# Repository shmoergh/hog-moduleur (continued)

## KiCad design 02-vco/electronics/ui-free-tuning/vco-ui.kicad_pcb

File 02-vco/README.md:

# Hog Moduleur / VCO

Eurorack compatible VCO.

## Features

- Raw saw generator with classic waveshaper circuits. Triangle, saw and square outputs
- Sub oscillator and noise circuit (can be selected with a jumper)
- Pulse width voltage control for square wave
- High precision over about 10 octaves
- Hard sync input
- FM input
- Two temperature compensation options for flexible DIY build (one is THT only)
- Separate core and UI PCBs for reusability and custom UI builds
- Gerber files for JLCPCB order
- Designed from very common electronic components

## Photos

**IN PROGRESS**

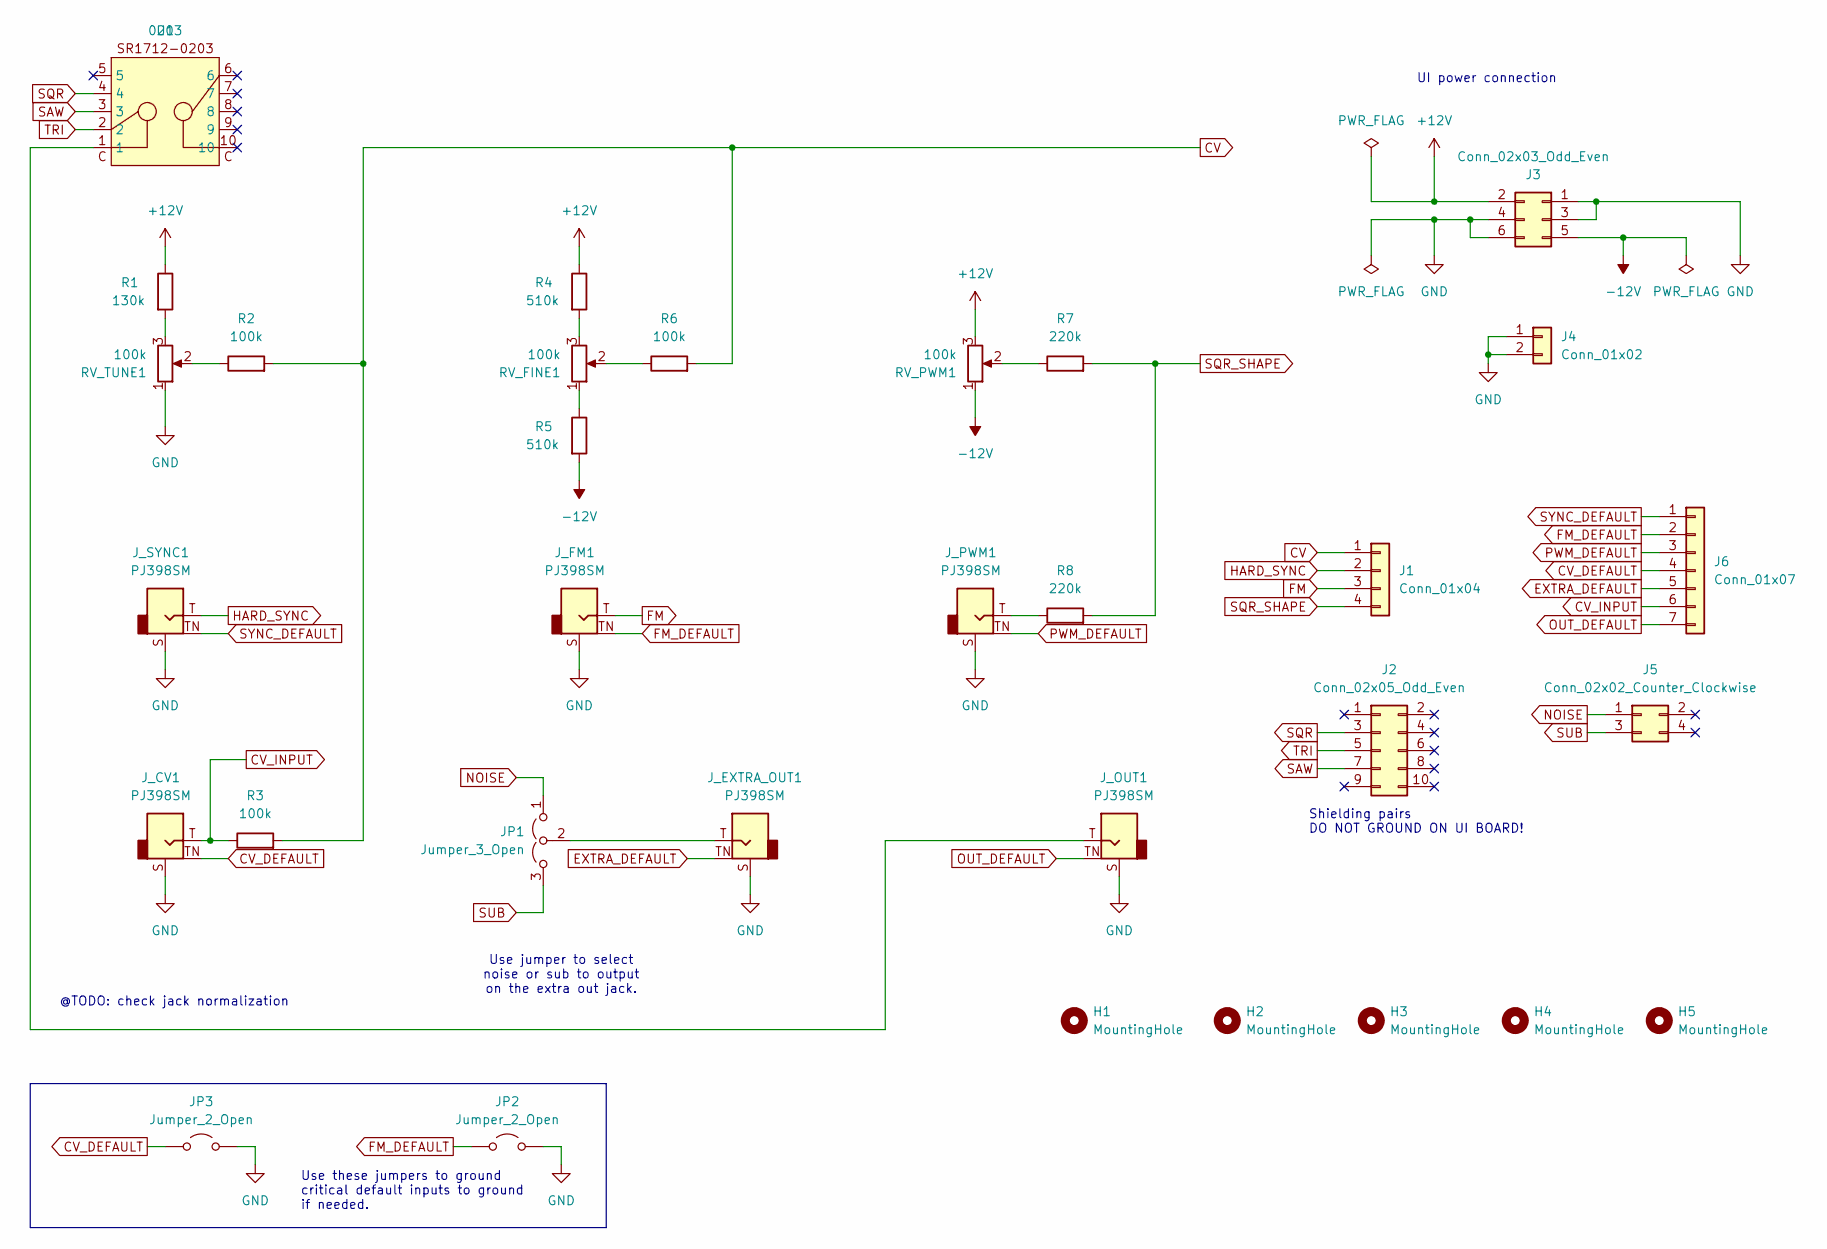
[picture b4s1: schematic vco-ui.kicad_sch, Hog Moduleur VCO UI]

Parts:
H1, H2, H3, H4, H5: MountingHole; MountingHole_3.2mm_M3_DIN965_Pad
J1: Conn_01x04; PinSocket_1x04_P2.54mm_Vertical; Part no. 200-SSW10401TMS
J2: Conn_02x05_Odd_Even; PinSocket_2x05_P2.54mm_Vertical; Part no. 200-SSW10501TD
J3: Conn_02x03_Odd_Even; PinSocket_2x03_P2.54mm_Vertical; Part no. 200-SSW10301TD
J4: Conn_01x02; PinSocket_1x02_P2.54mm_Vertical; Part no. 200-SSW10201TS
J5: Conn_02x02_Counter_Clockwise; PinSocket_2x02_P2.54mm_Vertical; Part no. 200-SSW10206TD
J6: Conn_01x07; PinSocket_1x07_P2.54mm_Vertical; Part no. 200-SSW10601TS
JP1: Jumper_3_Open; PinHeader_1x03_P2.54mm_Horizontal; Part no. 200-HTSW10308TSRA
JP2, JP3: Jumper_2_Open; PinHeader_1x02_P2.54mm_Horizontal; Part no. 200-HTSW10208TSRA
J_CV1: PJ398SM; Jack_3.5mm_QingPu_WQP-PJ398SM_Vertical_CircularHoles; Part no. PJ398SM
J_EXTRA_OUT1: PJ398SM; Jack_3.5mm_QingPu_WQP-PJ398SM_Vertical_CircularHoles; Part no. PJ398SM
J_FM1: PJ398SM; Jack_3.5mm_QingPu_WQP-PJ398SM_Vertical_CircularHoles; Part no. PJ398SM
J_OUT1: PJ398SM; Jack_3.5mm_QingPu_WQP-PJ398SM_Vertical_CircularHoles; Part no. PJ398SM
J_PWM1: PJ398SM; Jack_3.5mm_QingPu_WQP-PJ398SM_Vertical_CircularHoles; Part no. PJ398SM
J_SYNC1: PJ398SM; Jack_3.5mm_QingPu_WQP-PJ398SM_Vertical_CircularHoles; Part no. PJ398SM
R1: 130k; R_Axial_DIN0207_L6.3mm_D2.5mm_P7.62mm_Horizontal
R2, R3, R6: 100k; R_Axial_DIN0207_L6.3mm_D2.5mm_P7.62mm_Horizontal; Part no. 603-MFR-25FRF52100K
R4, R5: 510k; R_Axial_DIN0207_L6.3mm_D2.5mm_P7.62mm_Horizontal
R7, R8: 220k; R_Axial_DIN0207_L6.3mm_D2.5mm_P7.62mm_Horizontal; Part no. 603-MFR-25FRF52-220K
RV_FINE1: 100k; Potentiometer_Bourns_Single-PTV09A; Part no. 652-PTV09A4025FB104
RV_PWM1: 100k; Potentiometer_Bourns_Single-PTV09A; Part no. 652-PTV09A4025FB104
RV_TUNE1: 100k; Potentiometer_Bourns_Single-PTV09A; Part no. 652-PTV09A4025FB104
U1: 0203; SR1712-0203; Part no. 105-SR1712F-23NS

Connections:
+12V: J3.2, R1.1, R4.1, RV_PWM1.3
-12V: J3.5, R5.2, RV_PWM1.1
CV: J1.1, R2.2, R3.2, R6.2
CV_DEFAULT: J6.4, JP3.1 (A), J_CV1.TN
CV_INPUT: J6.6, J_CV1.T, R3.1
EXTRA_DEFAULT: J6.5, J_EXTRA_OUT1.TN
FM: J1.3, J_FM1.T
FM_DEFAULT: J6.2, JP2.1 (A), J_FM1.TN
GND: J3.1, J3.3, J3.4, J3.6, J4.1, J4.2, JP2.2 (B), JP3.2 (B), J_CV1.S, J_EXTRA_OUT1.S, J_FM1.S, J_OUT1.S, J_PWM1.S, J_SYNC1.S, RV_TUNE1.1
HARD_SYNC: J1.2, J_SYNC1.T
NOISE: J5.1, JP1.1 (A)
unnamed: JP1.2 (C), J_EXTRA_OUT1.T
unnamed: J_OUT1.T, U1.1
unnamed: J_PWM1.T, R8.1
unnamed: R1.2, RV_TUNE1.3
unnamed: R2.1, RV_TUNE1.2
unnamed: R4.2, RV_FINE1.3
unnamed: R5.1, RV_FINE1.1
unnamed: R6.1, RV_FINE1.2
unnamed: R7.1, RV_PWM1.2
OUT_DEFAULT: J6.7, J_OUT1.TN
PWM_DEFAULT: J6.3, J_PWM1.TN
SAW: J2.7, U1.3
SQR: J2.3, U1.4
SQR_SHAPE: J1.4, R7.2, R8.2
SUB: J5.3, JP1.3 (B)
SYNC_DEFAULT: J6.1, J_SYNC1.TN
TRI: J2.5, U1.2

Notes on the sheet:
@TODO: check jack normalization
Use these jumpers to ground critical default inputs to ground if needed.
UI power connection
Use jumper to select noise or sub to output on the extra out jack.
Shielding pairs DO NOT GROUND ON UI BOARD!

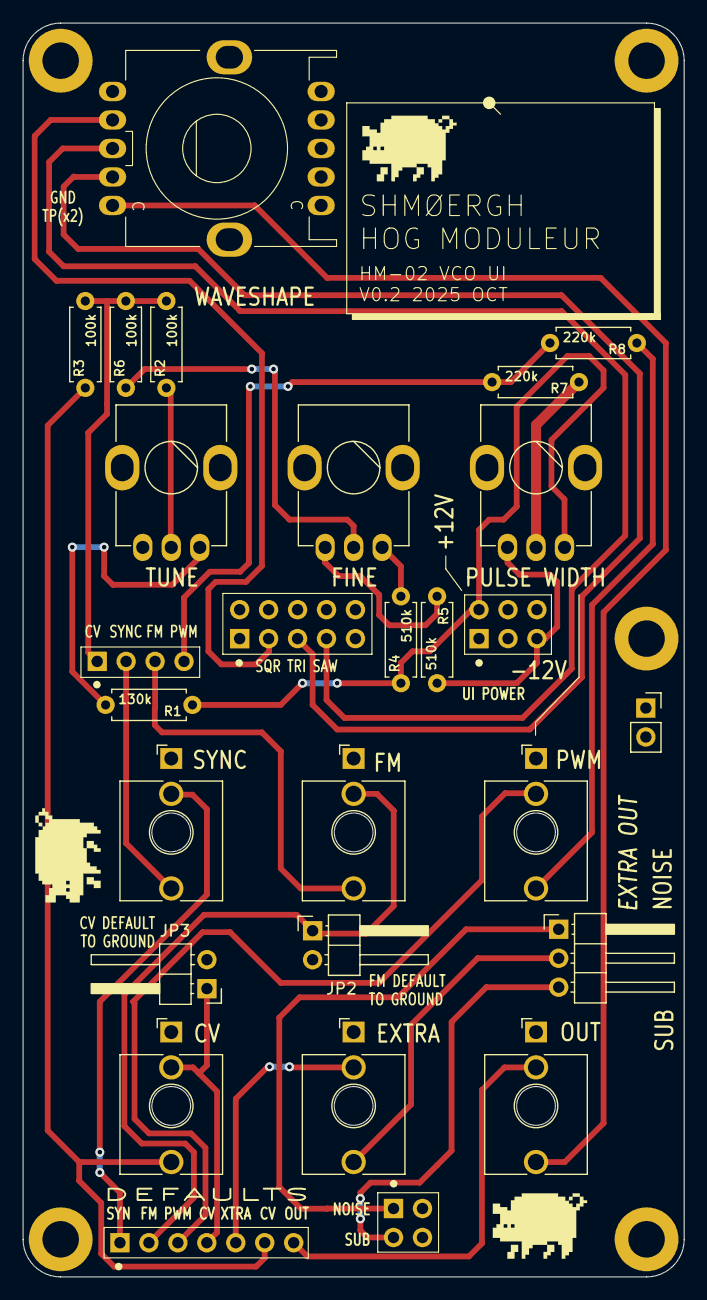
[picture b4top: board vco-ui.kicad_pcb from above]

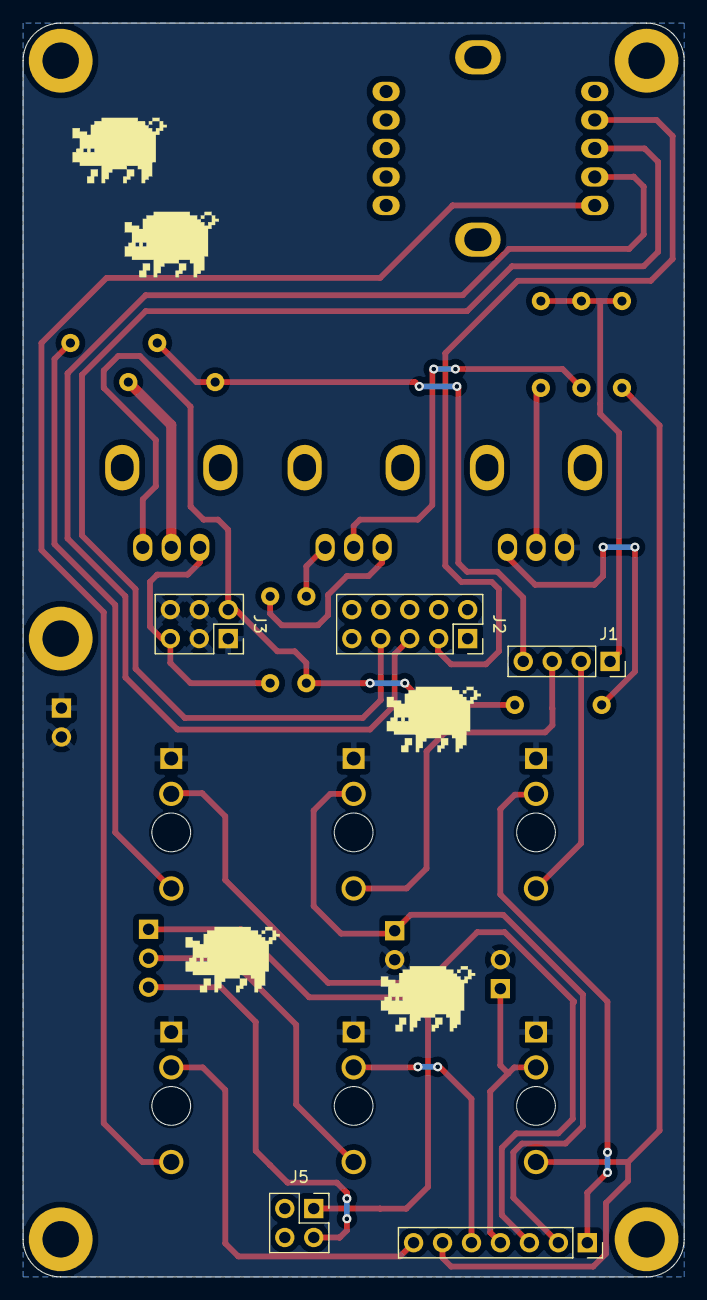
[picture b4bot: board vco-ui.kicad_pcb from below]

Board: 2 copper layers, 58.0 x 110.0 mm, 32 parts (5 on the bottom side), 28 nets.

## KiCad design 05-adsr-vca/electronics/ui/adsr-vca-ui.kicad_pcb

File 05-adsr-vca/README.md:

# Hog Moduleur / ADSR + VCA

TBD

## Status

**IN PROGRESS**

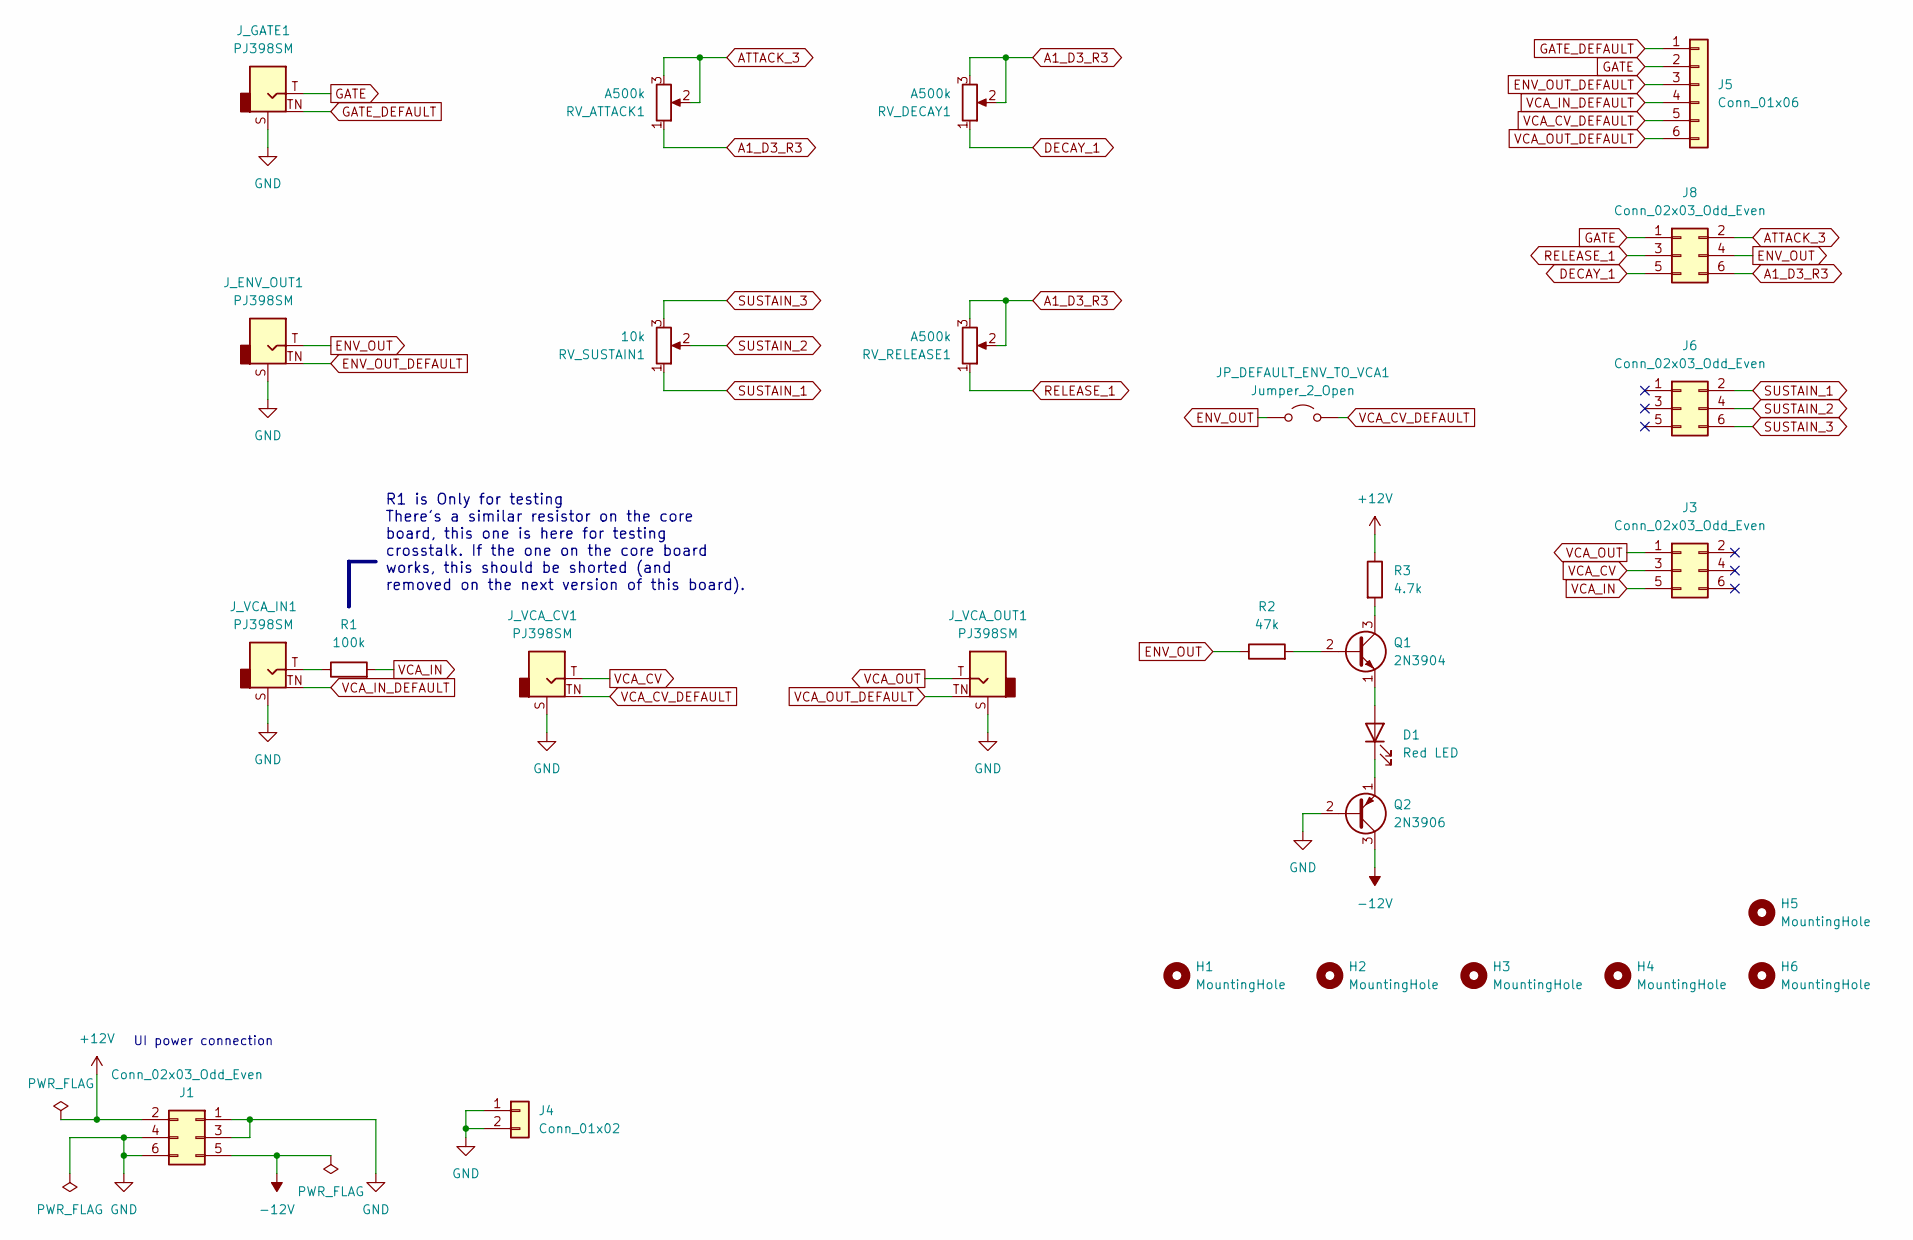
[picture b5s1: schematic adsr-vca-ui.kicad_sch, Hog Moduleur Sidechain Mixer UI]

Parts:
D1: Red LED; LED_D3.0mm
H1, H2, H3, H4, H5, H6: MountingHole; MountingHole_3.2mm_M3_DIN965_Pad
J1: Conn_02x03_Odd_Even; PinSocket_2x03_P2.54mm_Vertical; Part no. 200-SSW10301TD
J3, J6, J8: Conn_02x03_Odd_Even; PinSocket_2x03_P2.54mm_Vertical
J4: Conn_01x02; PinSocket_1x02_P2.54mm_Vertical; Part no. 200-SSW10201TS
J5: Conn_01x06; PinSocket_1x06_P2.54mm_Vertical; Part no. 200-SSW10601TS
JP_DEFAULT_ENV_TO_VCA1: Jumper_2_Open; PinHeader_1x02_P2.54mm_Horizontal
J_ENV_OUT1: PJ398SM; Jack_3.5mm_QingPu_WQP-PJ398SM_Vertical_CircularHoles; Part no. PJ398SM
J_GATE1: PJ398SM; Jack_3.5mm_QingPu_WQP-PJ398SM_Vertical_CircularHoles; Part no. PJ398SM
J_VCA_CV1: PJ398SM; Jack_3.5mm_QingPu_WQP-PJ398SM_Vertical_CircularHoles; Part no. PJ398SM
J_VCA_IN1: PJ398SM; Jack_3.5mm_QingPu_WQP-PJ398SM_Vertical_CircularHoles; Part no. PJ398SM
J_VCA_OUT1: PJ398SM; Jack_3.5mm_QingPu_WQP-PJ398SM_Vertical_CircularHoles; Part no. PJ398SM
Q1: 2N3904; TO-92_Inline_Wide
Q2: 2N3906; TO-92_Inline_Wide
R1: 100k; R_Axial_DIN0207_L6.3mm_D2.5mm_P7.62mm_Horizontal
R2: 47k; R_Axial_DIN0207_L6.3mm_D2.5mm_P7.62mm_Horizontal
R3: 4.7k; R_Axial_DIN0207_L6.3mm_D2.5mm_P7.62mm_Horizontal
RV_ATTACK1: A500k; Potentiometer_Bourns_Single-PTV09A; Part no. 652-PTV09A4025FB104
RV_DECAY1: A500k; Potentiometer_Bourns_Single-PTV09A; Part no. 652-PTV09A4025FB104
RV_RELEASE1: A500k; Potentiometer_Bourns_Single-PTV09A; Part no. 652-PTV09A4025FB104
RV_SUSTAIN1: 10k; TRIM_PTA4543-2015DPB103; Part no. 652-PTV09A4025FB104

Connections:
+12V: J1.2, R3.1
-12V: J1.5, Q2.3 (C)
A1_D3_R3: J8.6, RV_ATTACK1.1, RV_DECAY1.2, RV_DECAY1.3, RV_RELEASE1.2, RV_RELEASE1.3
ATTACK_3: J8.2, RV_ATTACK1.2, RV_ATTACK1.3
DECAY_1: J8.5, RV_DECAY1.1
ENV_OUT: J8.4, JP_DEFAULT_ENV_TO_VCA1.1 (A), J_ENV_OUT1.T, R2.1
ENV_OUT_DEFAULT: J5.3, J_ENV_OUT1.TN
GATE: J5.2, J8.1, J_GATE1.T
GATE_DEFAULT: J5.1, J_GATE1.TN
GND: J1.1, J1.3, J1.4, J1.6, J4.1, J4.2, J_ENV_OUT1.S, J_GATE1.S, J_VCA_CV1.S, J_VCA_IN1.S, J_VCA_OUT1.S, Q2.2 (B)
unnamed: D1.2 (A), Q1.1 (E)
unnamed: D1.1 (K), Q2.1 (E)
unnamed: J_VCA_IN1.T, R1.1
unnamed: Q1.2 (B), R2.2
unnamed: Q1.3 (C), R3.2
RELEASE_1: J8.3, RV_RELEASE1.1
SUSTAIN_1: J6.2, RV_SUSTAIN1.1
SUSTAIN_2: J6.4, RV_SUSTAIN1.2
SUSTAIN_3: J6.6, RV_SUSTAIN1.3
VCA_CV: J3.3, J_VCA_CV1.T
VCA_CV_DEFAULT: J5.5, JP_DEFAULT_ENV_TO_VCA1.2 (B), J_VCA_CV1.TN
VCA_IN: J3.5, R1.2
VCA_IN_DEFAULT: J5.4, J_VCA_IN1.TN
VCA_OUT: J3.1, J_VCA_OUT1.T
VCA_OUT_DEFAULT: J5.6, J_VCA_OUT1.TN

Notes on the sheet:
R1 is Only for testing There's a similar resistor on the core board, this one is here for testing crosstalk. If the one on the core board works, this should be shorted (and removed on the next version of this board).
UI power connection

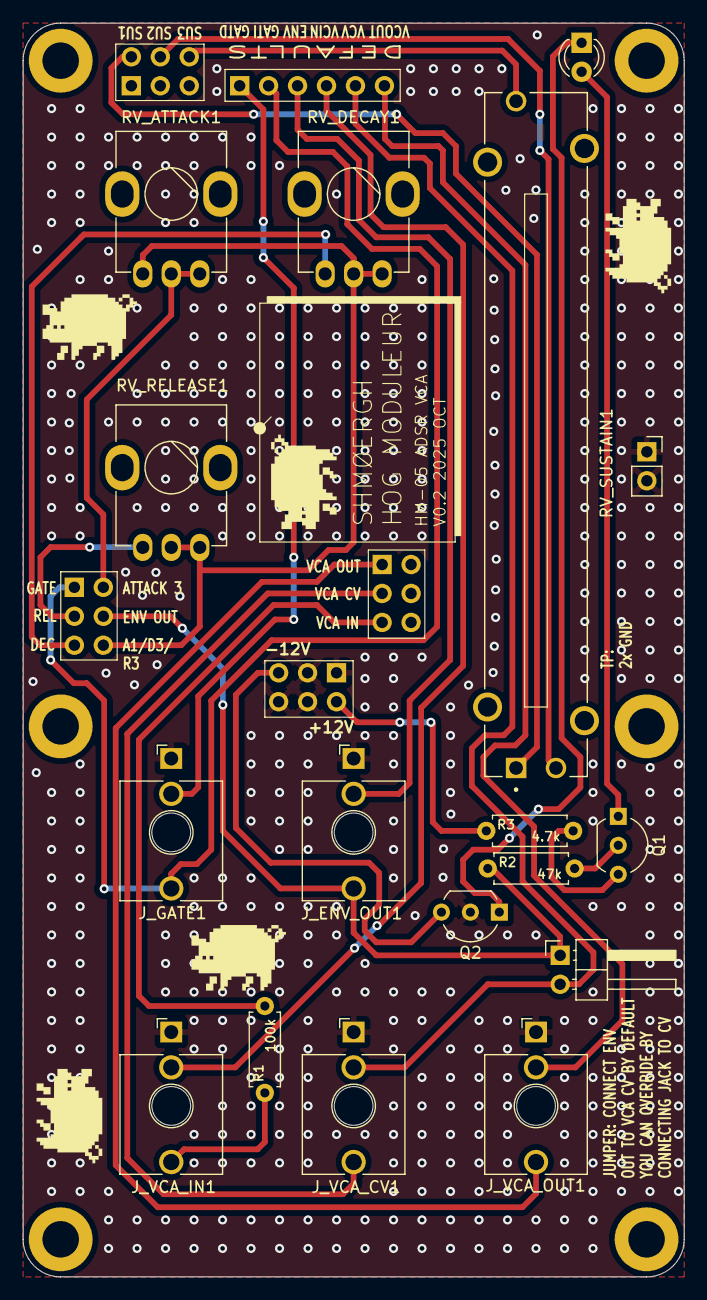
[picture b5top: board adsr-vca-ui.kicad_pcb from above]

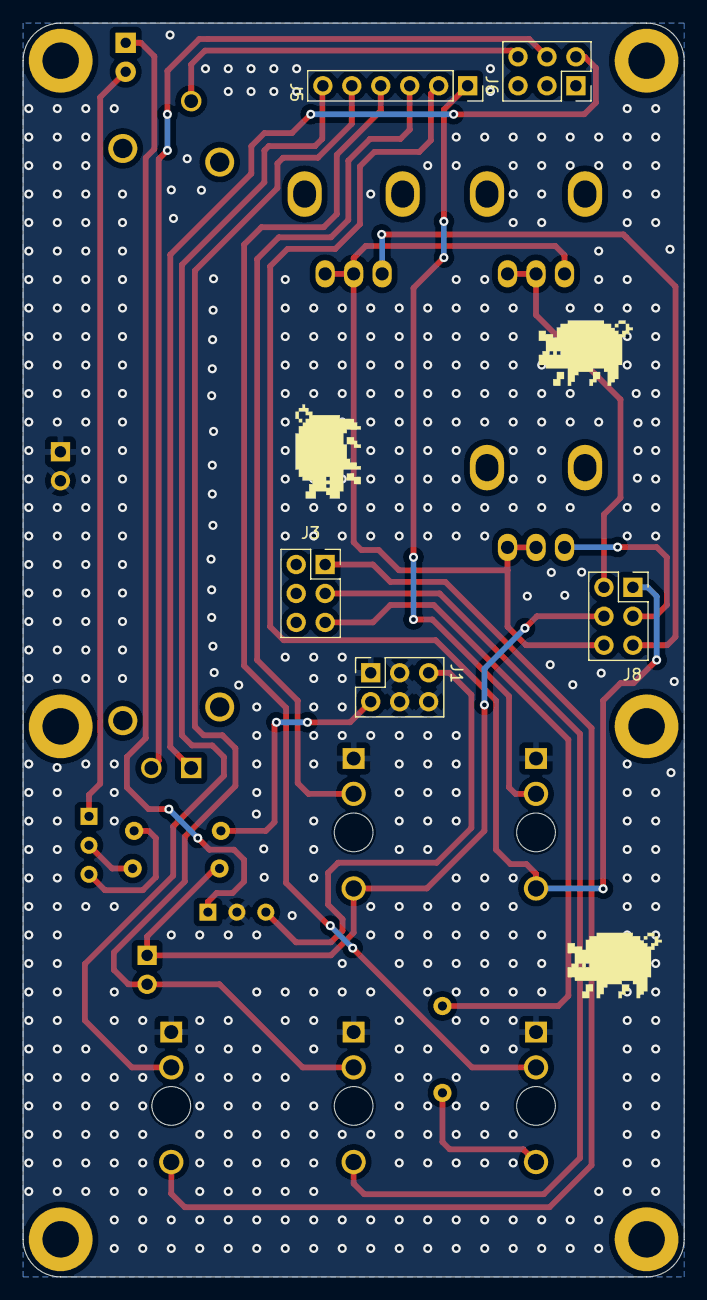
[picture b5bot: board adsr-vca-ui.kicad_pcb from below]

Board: 2 copper layers, 58.0 x 110.0 mm, 28 parts (5 on the bottom side), 25 nets.

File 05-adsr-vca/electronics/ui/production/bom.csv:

Designator,Footprint,Quantity,Value,LCSC Part #
D1,LED_D3.0mm,1,D,
"J1, J3, J6, J8",PinSocket_2x03_P2.54mm_Vertical,4,Conn_02x03_Odd_Even,
J4,PinSocket_1x02_P2.54mm_Vertical,1,Conn_01x02,
J5,PinSocket_1x06_P2.54mm_Vertical,1,Conn_01x06,
JP_DEFAULT_ENV_TO_VCA1,PinHeader_1x02_P2.54mm_Horizontal,1,Jumper_2_Open,
"J_ENV_OUT1, J_GATE1, J_VCA_CV1, J_VCA_IN1, J_VCA_OUT1",Jack_3.5mm_QingPu_WQP-PJ398SM_Vertical_CircularHoles,5,PJ398SM,
"RV_ATTACK1, RV_DECAY1, RV_RELEASE1",Potentiometer_Bourns_Single-PTV09A,3,A500k,
RV_SUSTAIN1,TRIM_PTA4543-2015DPB103,1,10k,

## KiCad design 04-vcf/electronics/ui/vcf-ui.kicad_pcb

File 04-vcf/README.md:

# Hog Moduleur / VCF

Dual mode Eurorack compatible diode filter based on the famous Synthacon Steiner-Parker circuit.

## Features

- Classic diode filter with extremely drippy character
- Low pass and high pass filter inputs
- Fine-tunable maximum resonance control — can go smooth to crazy
- Two external CV inputs with logarithmic attenuverters
- Optional EMC shielding to isolate external noise
- Separate core and UI PCBs for reusability and custom UI builds
- Gerber files for JLCPCB order
- Designed from very common electronic components

## Photos

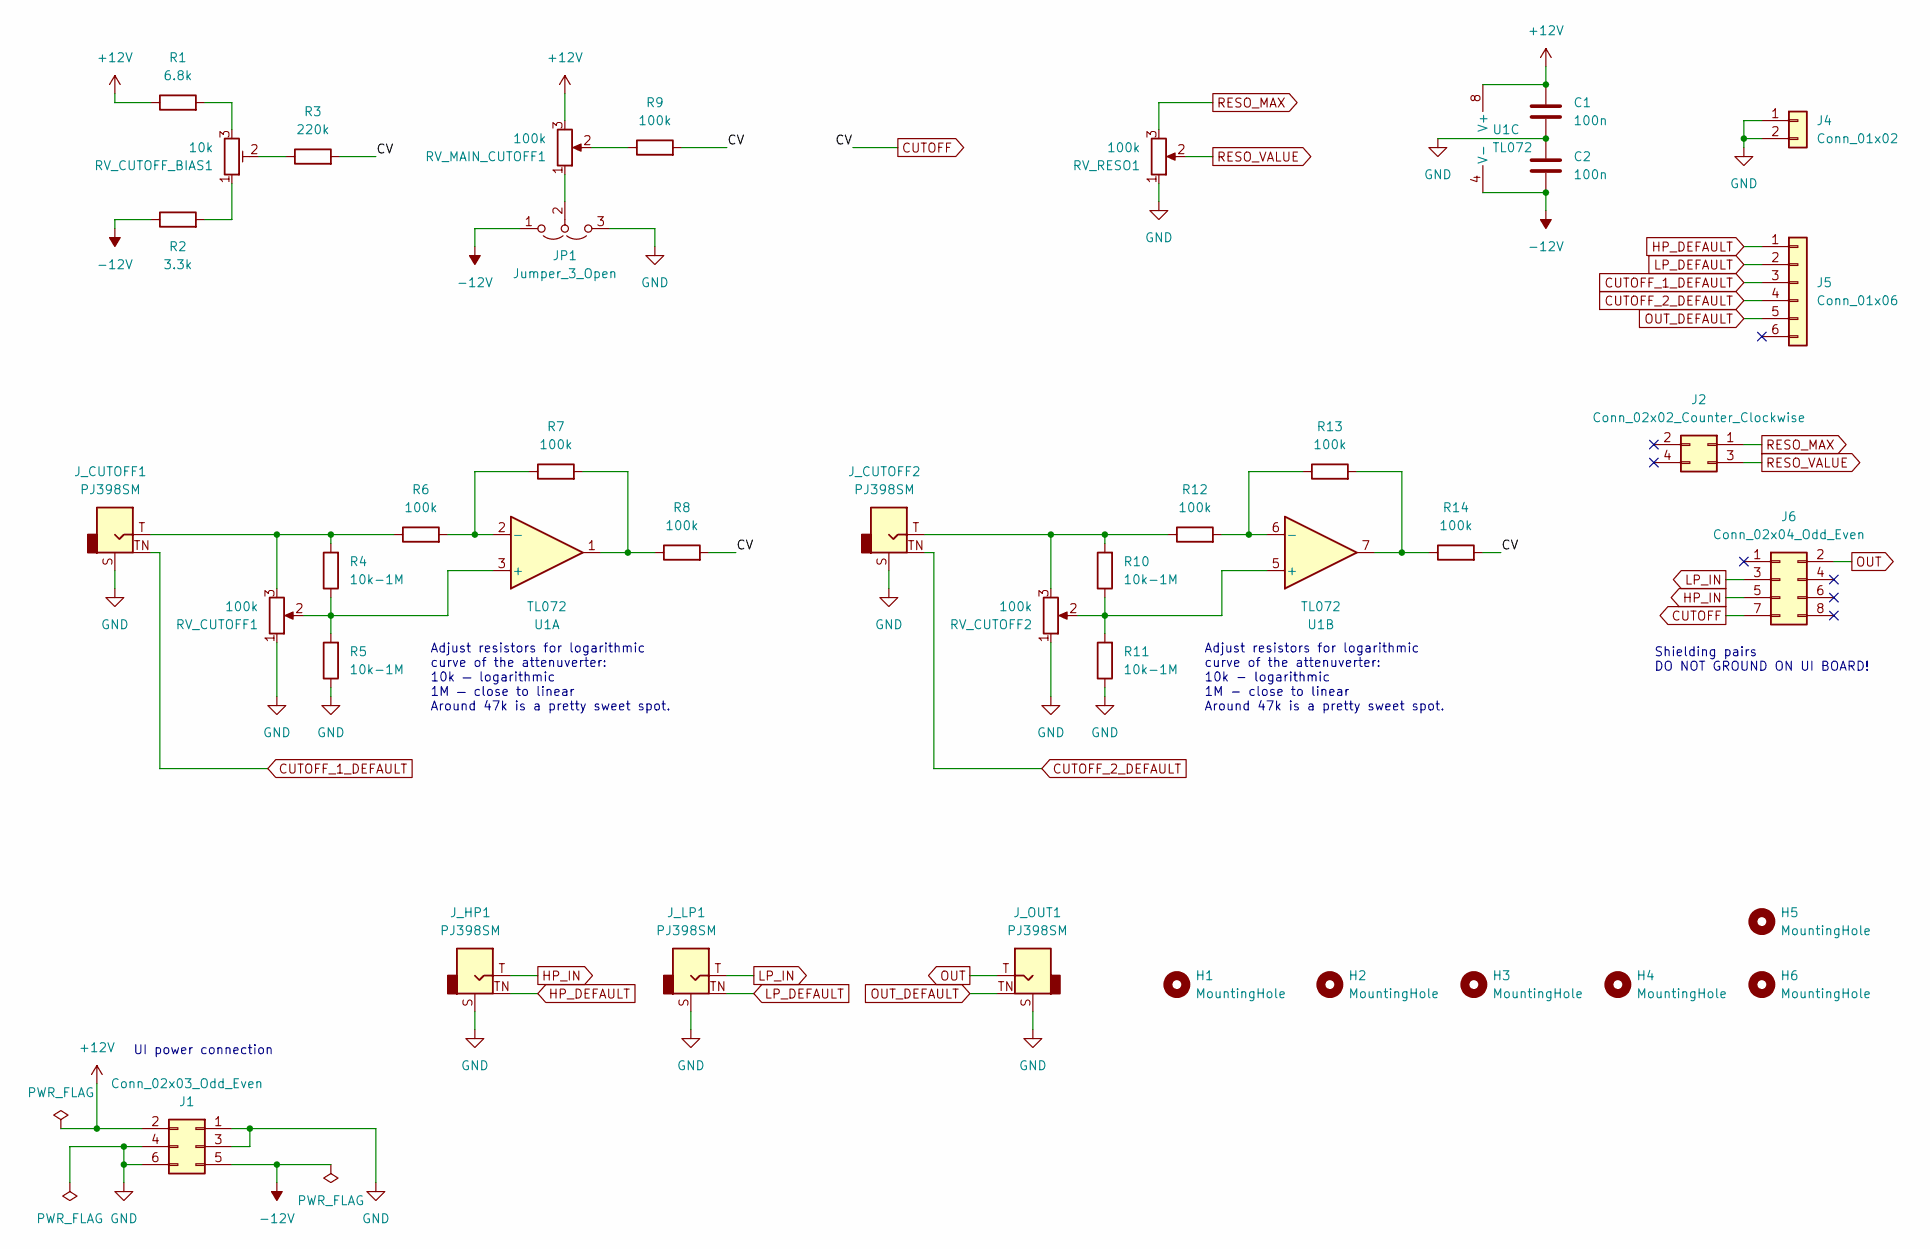
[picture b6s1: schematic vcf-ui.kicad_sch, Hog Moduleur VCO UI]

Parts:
C1, C2: 100n; C_Disc_D5.0mm_W2.5mm_P2.50mm
H1, H2, H3, H4, H5, H6: MountingHole; MountingHole_3.2mm_M3_DIN965_Pad
J1: Conn_02x03_Odd_Even; PinSocket_2x03_P2.54mm_Vertical; Part no. 200-SSW10301TD
J2: Conn_02x02_Counter_Clockwise; PinSocket_2x02_P2.54mm_Vertical; Part no. 200-SSW10206TD
J4: Conn_01x02; PinSocket_1x02_P2.54mm_Vertical; Part no. 200-SSW10201TS
J5: Conn_01x06; PinSocket_1x06_P2.54mm_Vertical; Part no. 200-SSW10601TS
J6: Conn_02x04_Odd_Even; PinSocket_2x04_P2.54mm_Vertical
JP1: Jumper_3_Open; PinHeader_1x03_P2.54mm_Vertical
J_CUTOFF1, J_CUTOFF2: PJ398SM; Jack_3.5mm_QingPu_WQP-PJ398SM_Vertical_CircularHoles; Part no. PJ398SM
J_HP1: PJ398SM; Jack_3.5mm_QingPu_WQP-PJ398SM_Vertical_CircularHoles; Part no. PJ398SM
J_LP1: PJ398SM; Jack_3.5mm_QingPu_WQP-PJ398SM_Vertical_CircularHoles; Part no. PJ398SM
J_OUT1: PJ398SM; Jack_3.5mm_QingPu_WQP-PJ398SM_Vertical_CircularHoles; Part no. PJ398SM
R1: 6.8k; R_Axial_DIN0207_L6.3mm_D2.5mm_P7.62mm_Horizontal; Part no. 603-MFR-25FRF52100K
R2: 3.3k; R_Axial_DIN0207_L6.3mm_D2.5mm_P7.62mm_Horizontal; Part no. 603-MFR-25FRF52100K
R3: 220k; R_Axial_DIN0207_L6.3mm_D2.5mm_P7.62mm_Horizontal; Part no. 603-MFR-25FRF52100K
R4, R5, R10, R11: 10k-1M; R_Axial_DIN0207_L6.3mm_D2.5mm_P7.62mm_Horizontal; Part no. 603-MFR-25FRF52100K
R6, R7, R8, R12, R13, R14: 100k; R_Axial_DIN0207_L6.3mm_D2.5mm_P7.62mm_Horizontal; Part no. 603-MFR-25FRF52100K
R9: 100k; R_Axial_DIN0207_L6.3mm_D2.5mm_P7.62mm_Horizontal; Part no. 603-MFR-25FRF52-220K
RV_CUTOFF1, RV_CUTOFF2: 100k; Potentiometer_Bourns_Single-PTV09A; Part no. 652-PTV09A4025FB104
RV_CUTOFF_BIAS1: 10k; Potentiometer_ACP_CA6-H2,5_Horizontal
RV_MAIN_CUTOFF1: 100k; Potentiometer_Bourns_Single-PTV09A; Part no. 652-PTV09A4025FB104
RV_RESO1: 100k; Potentiometer_Bourns_Single-PTV09A; Part no. 652-PTV09A4025FB104
U1: TL072; DIP-8_W7.62mm_LongPads

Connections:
+12V: C1.1, J1.2, R1.1, RV_MAIN_CUTOFF1.3, U1.8 (V+)
-12V: C2.2, J1.5, JP1.1 (A), R2.1, U1.4 (V-)
CUTOFF: J6.7, R3.2, R8.2, R9.2, R14.2
CUTOFF_1_DEFAULT: J5.3, J_CUTOFF1.TN
CUTOFF_2_DEFAULT: J5.4, J_CUTOFF2.TN
GND: C1.2, C2.1, J1.1, J1.3, J1.4, J1.6, J4.1, J4.2, JP1.3 (B), J_CUTOFF1.S, J_CUTOFF2.S, J_HP1.S, J_LP1.S, J_OUT1.S, R5.1, R11.1, RV_CUTOFF1.1, RV_CUTOFF2.1, RV_RESO1.1
HP_DEFAULT: J5.1, J_HP1.TN
HP_IN: J6.5, J_HP1.T
LP_DEFAULT: J5.2, J_LP1.TN
LP_IN: J6.3, J_LP1.T
unnamed: JP1.2 (C), RV_MAIN_CUTOFF1.1
unnamed: J_CUTOFF1.T, R4.2, R6.1, RV_CUTOFF1.3
unnamed: J_CUTOFF2.T, R10.2, R12.1, RV_CUTOFF2.3
unnamed: R1.2, RV_CUTOFF_BIAS1.3
unnamed: R2.2, RV_CUTOFF_BIAS1.1
unnamed: R3.1, RV_CUTOFF_BIAS1.2
unnamed: R7.2, R8.1, U1.1
unnamed: R9.1, RV_MAIN_CUTOFF1.2
unnamed: R13.2, R14.1, U1.7
unnamed: R4.1, R5.2, RV_CUTOFF1.2, U1.3 (+)
unnamed: R6.2, R7.1, U1.2 (-)
unnamed: R10.1, R11.2, RV_CUTOFF2.2, U1.5 (+)
unnamed: R12.2, R13.1, U1.6 (-)
OUT: J6.2, J_OUT1.T
OUT_DEFAULT: J5.5, J_OUT1.TN
RESO_MAX: J2.1, RV_RESO1.3
RESO_VALUE: J2.3, RV_RESO1.2

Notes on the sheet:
UI power connection
Adjust resistors for logarithmic curve of the attenuverter: 10k — logarithmic 1M — close to linear Around 47k is a pretty sweet spot.
Shielding pairs DO NOT GROUND ON UI BOARD!
Adjust resistors for logarithmic curve of the attenuverter: 10k - logarithmic 1M - close to linear Around 47k is a pretty sweet spot.

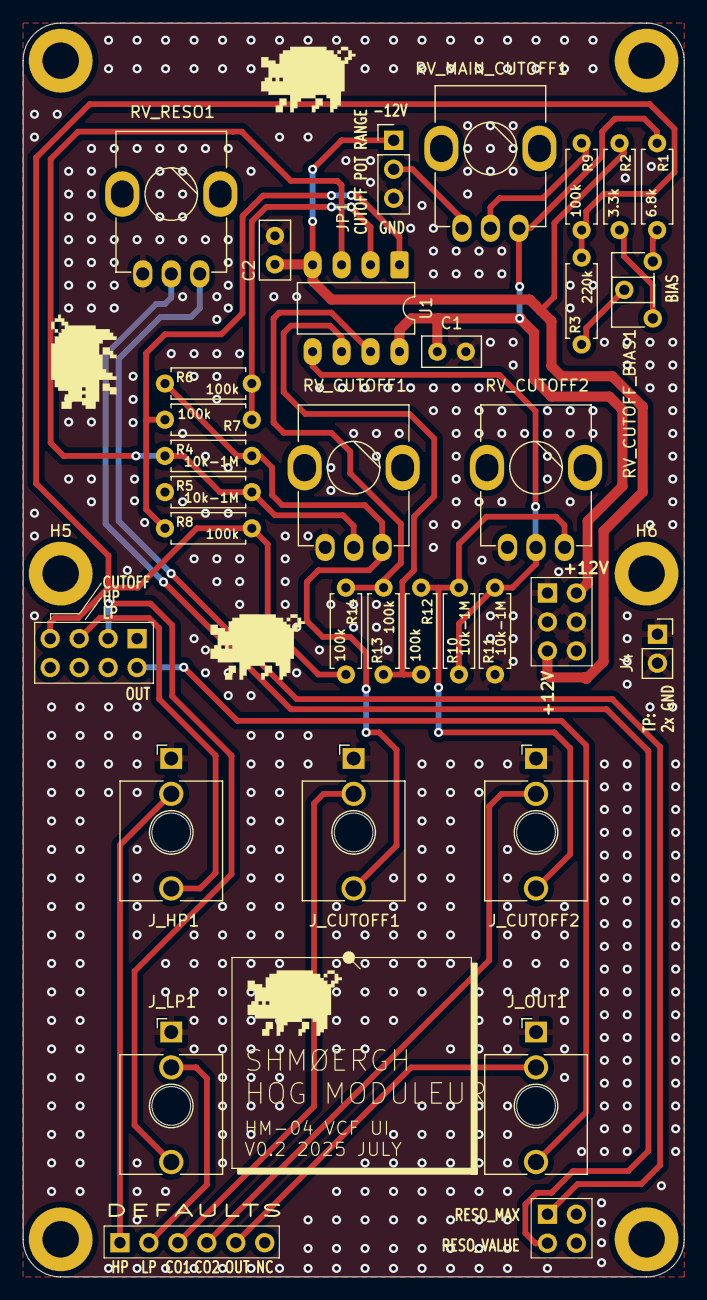
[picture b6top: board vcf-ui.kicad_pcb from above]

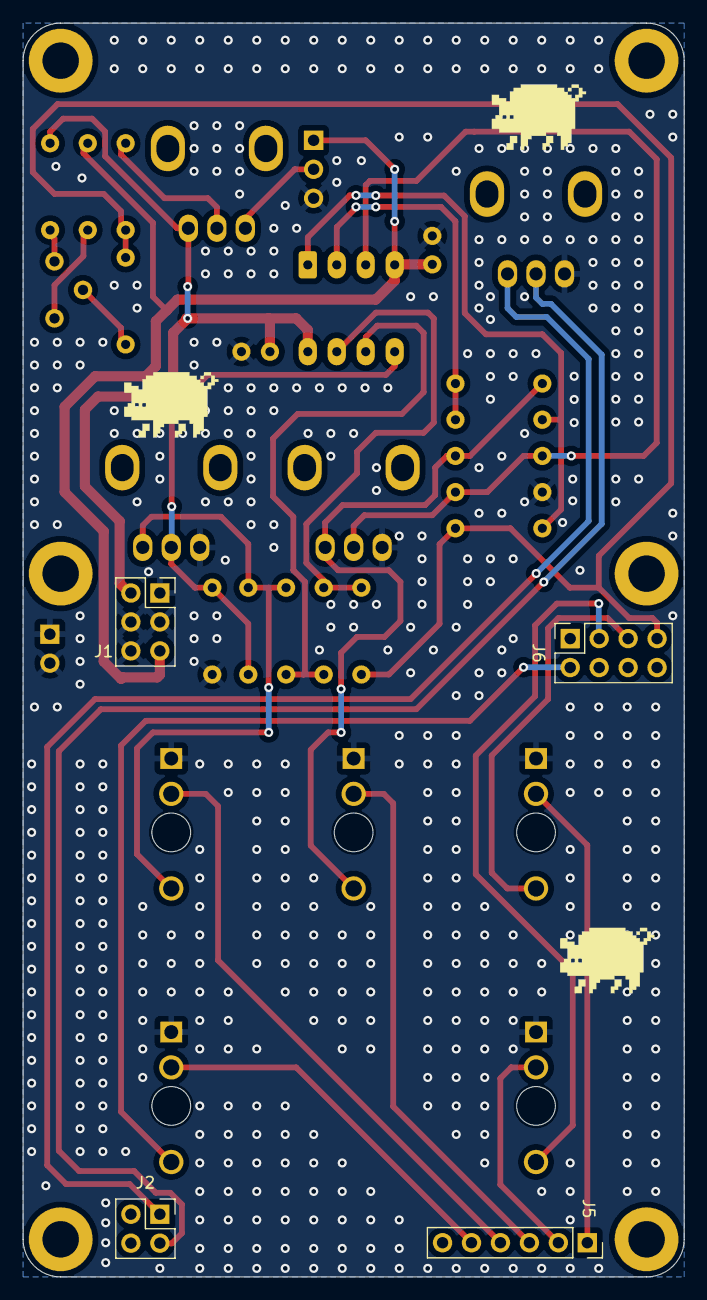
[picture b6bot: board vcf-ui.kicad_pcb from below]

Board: 2 copper layers, 58.0 x 110.0 mm, 39 parts (4 on the bottom side), 27 nets.

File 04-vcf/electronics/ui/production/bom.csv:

Designator,Footprint,Quantity,Value,LCSC Part #
"C1, C2",C_Disc_D5.0mm_W2.5mm_P2.50mm,2,C,
J1,PinSocket_2x03_P2.54mm_Vertical,1,Conn_02x03_Odd_Even,
J2,PinSocket_2x02_P2.54mm_Vertical,1,Conn_02x02_Counter_Clockwise,
J4,PinSocket_1x02_P2.54mm_Vertical,1,Conn_01x02,
J5,PinSocket_1x06_P2.54mm_Vertical,1,Conn_01x06,
J6,PinSocket_2x04_P2.54mm_Vertical,1,Conn_02x04_Odd_Even,
"J_CUTOFF1, J_CUTOFF2, J_HP1, J_LP1, J_OUT1",Jack_3.5mm_QingPu_WQP-PJ398SM_Vertical_CircularHoles,5,PJ398SM,
R1,R_Axial_DIN0207_L6.3mm_D2.5mm_P7.62mm_Horizontal,1,6.8k,
"R10, R11, R4, R5",R_Axial_DIN0207_L6.3mm_D2.5mm_P7.62mm_Horizontal,4,10k-1M,
"R12, R13, R14, R6, R7, R8, R9",R_Axial_DIN0207_L6.3mm_D2.5mm_P7.62mm_Horizontal,7,100k,
R2,R_Axial_DIN0207_L6.3mm_D2.5mm_P7.62mm_Horizontal,1,3.3k,
R3,R_Axial_DIN0207_L6.3mm_D2.5mm_P7.62mm_Horizontal,1,220k,
"RV_CUTOFF1, RV_CUTOFF2, RV_MAIN_CUTOFF1, RV_RESO1",Potentiometer_Bourns_Single-PTV09A,4,100k,
RV_CUTOFF_BIAS1,"Potentiometer_ACP_CA6-H2,5_Horizontal",1,10k,
U1,DIP-8_W7.62mm_LongPads,1,TL072,
